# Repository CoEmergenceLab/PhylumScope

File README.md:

# Mechanical Design

# Electronics

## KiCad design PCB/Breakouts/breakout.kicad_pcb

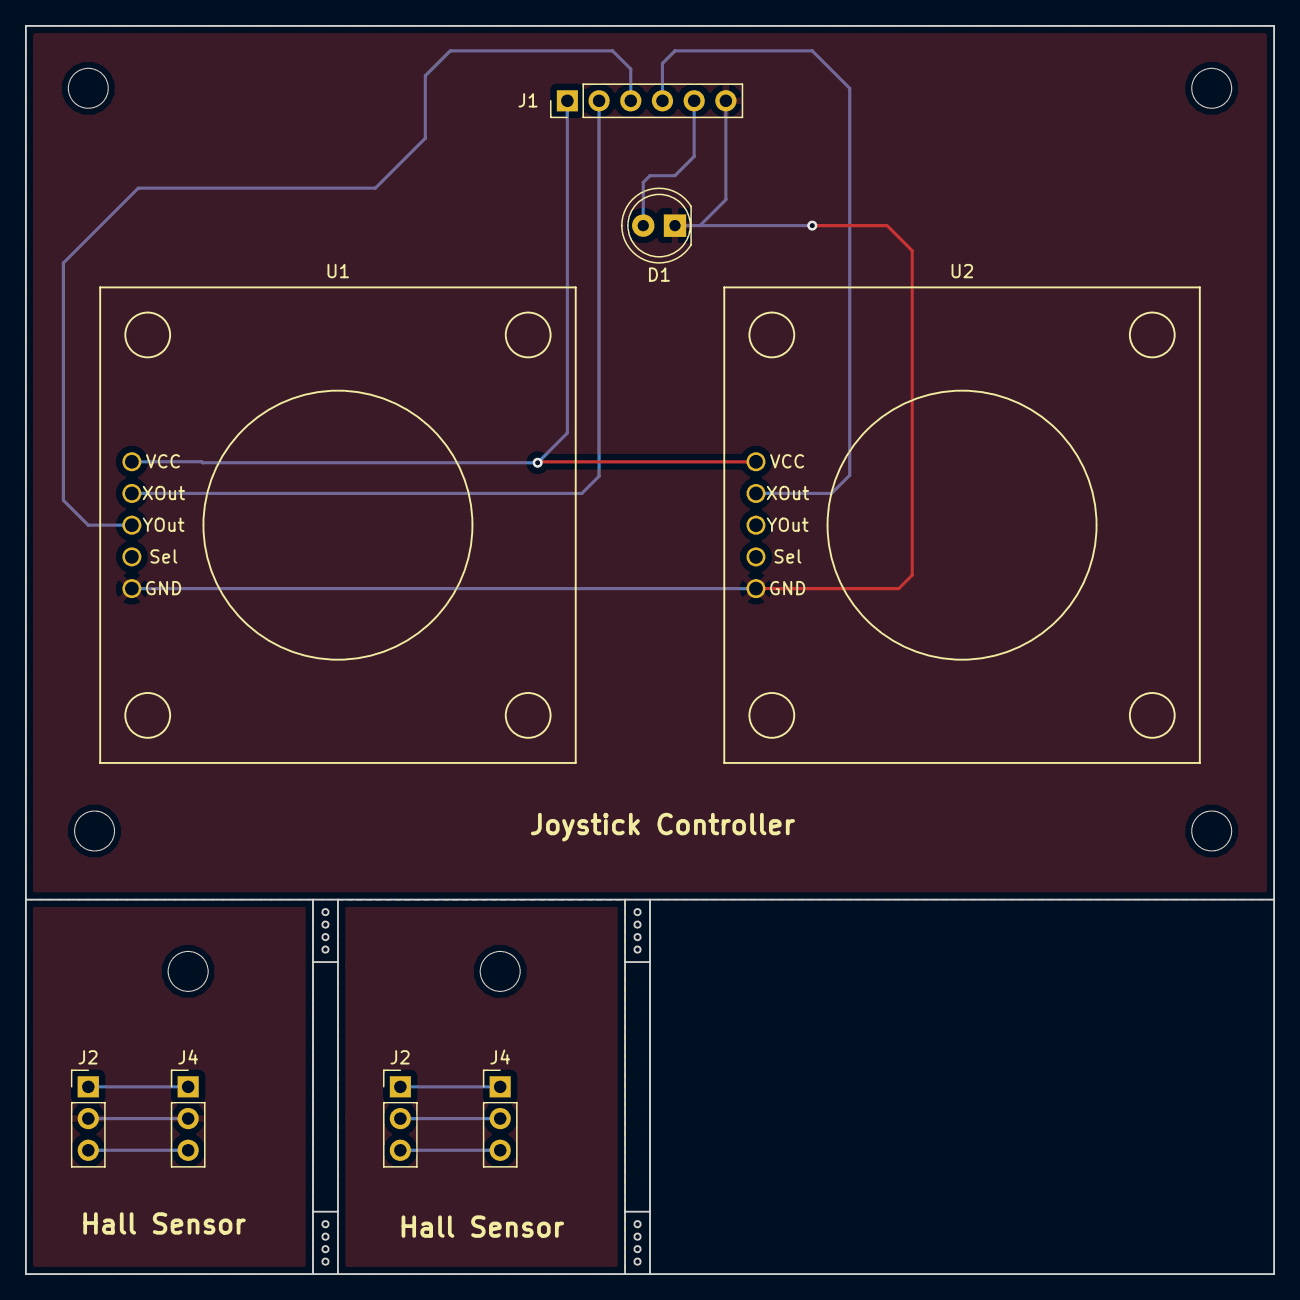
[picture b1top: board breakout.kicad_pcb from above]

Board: 2 copper layers, 100.0 x 100.0 mm, 8 parts (0 on the bottom side), 9 nets.

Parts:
D1: LED; LED_D5.0mm
J1: PinHeader_1x06_P2.54mm_Vertical
J2, J2#2: PinHeader_1x03_P2.54mm_Vertical
J4, J4#2: Hall; PinHeader_1x03_P2.54mm_Vertical
U1: Joystick_XY; ADA_joystick
U2: Joystick_Z; ADA_joystick

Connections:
unnamed: D1.1, J1.6, U1.5, U2.5
unnamed: D1.2, J1.5
unnamed: J1.1, U1.1, U2.1
unnamed: J1.2, U1.2
unnamed: J1.3, U1.3
unnamed: J1.4, U2.2
unnamed: J2#2.1, J4#2.1
unnamed: J2#2.2, J4#2.2
unnamed: J2#2.3, J4#2.3

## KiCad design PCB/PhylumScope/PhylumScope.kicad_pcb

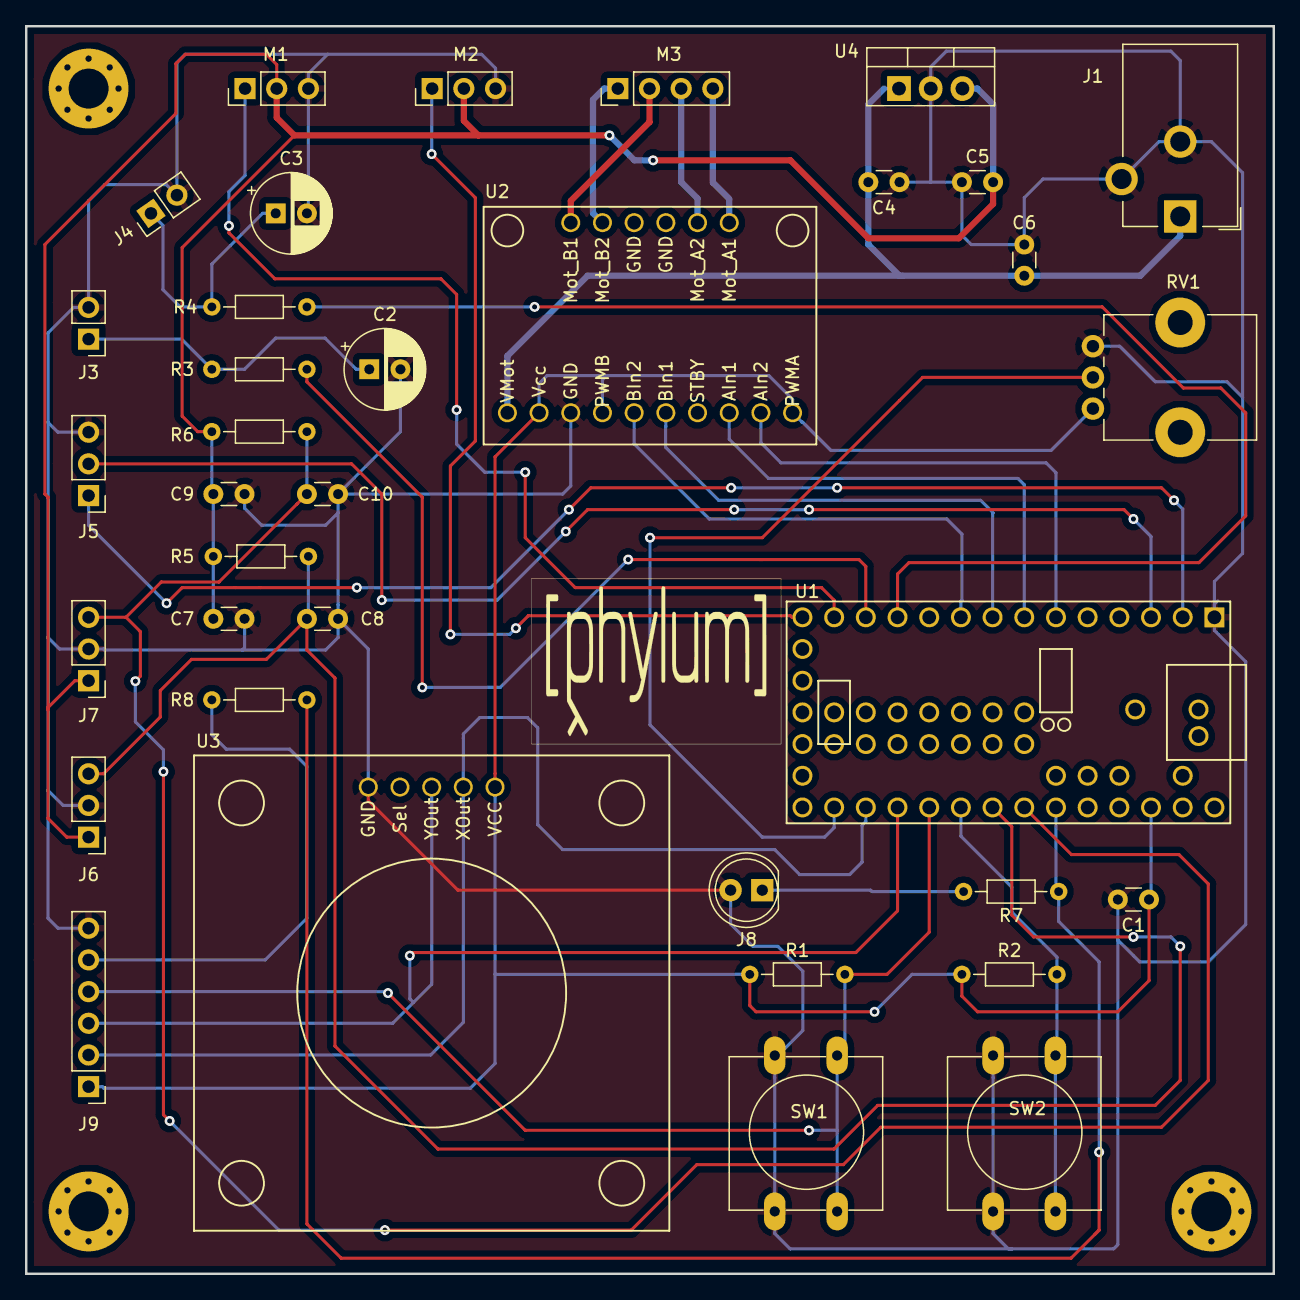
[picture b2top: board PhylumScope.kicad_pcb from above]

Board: 2 copper layers, 100.0 x 100.0 mm, 36 parts (0 on the bottom side), 30 nets.

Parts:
C1, C4, C5, C6: 0.1uF; C_Disc_D3.0mm_W1.6mm_P2.50mm
C2, C3: 47uF; CP_Radial_D6.3mm_P2.50mm
C7, C9: 100nF; C_Disc_D3.0mm_W1.6mm_P2.50mm
C8, C10: 4.7nF; C_Disc_D3.0mm_W1.6mm_P2.50mm
J1: +12V; BarrelJack_CUI_PJ-102AH_Horizontal
J3: LED2; PinHeader_1x02_P2.54mm_Vertical
J4: LED1; PinHeader_1x02_P2.54mm_Vertical
J5: RX/TX1; PinHeader_1x03_P2.54mm_Vertical
J6: Hall_L; PinHeader_1x03_P2.54mm_Vertical
J7: Hall_H; PinHeader_1x03_P2.54mm_Vertical
J8: LED3; LED_D5.0mm
J9: Controller; PinHeader_1x06_P2.54mm_Vertical
M1: Servo_X; PinHeader_1x03_P2.54mm_Vertical
M2: Servo_Y; PinHeader_1x03_P2.54mm_Vertical
M3: Stepper_Z; PinHeader_1x04_P2.54mm_Vertical
R1, R2, R5, R6: 10k; R_Axial_DIN0204_L3.6mm_D1.6mm_P7.62mm_Horizontal
R3, R4, R7, R8: 220Ω; R_Axial_DIN0204_L3.6mm_D1.6mm_P7.62mm_Horizontal
RV1: 10k; Potentiometer_Alps_RK09K_Single_Vertical
SW1: Z_UP; SW_PUSH-12mm
SW2: Z_DOWN; SW_PUSH-12mm
U1: Teensy3.2; Teensy30_31_32_All_Pins
U2: TB6612; ADA_TB6612
U3: Joystick; ADA_joystick
U4: LM7805; TO-220-3_Vertical

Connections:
+3.3V_bus: C1.1, J9.1, R1.1, R2.1, RV1.1, U1.31, U2.2, U2.4, U2.10, U3.1
+5V_bus: C5.2, C7.1, C9.1, J6.1, J7.1, M1.2, M2.2, R5.1, R6.1, U4.3
+12V_bus: C4.2, C6.2, J1.1, U2.1, U4.1
Btn_1: J9.4, R1.2, SW1.2, U1.24
Btn_2: R2.2, SW2.2, U1.25
GND: C1.2, C2.2, C3.2, C4.1, C5.1, C6.1, C7.2, C8.2, C9.2, C10.2, J1.2, J1.3, J3.2, J4.2, J5.3, J6.2, J7.2, J8.2, J9.6, M1.3, M2.3, RV1.3, SW1.1, SW2.1, U1.1, U2.3, U3.5, U4.2
Hall_H: C10.1, J7.3, R6.2, U1.27
Hall_L: C8.1, J6.3, R5.2, U1.26
Joy_X: J9.2, U1.22, U3.2
Joy_Y: J9.3, U1.23, U3.3
LED_1: R4.1, U1.11
LED_2: R3.1, U1.12
LED_3: R7.1, R8.1, U1.28
unnamed: C2.1, J3.1, R3.2
unnamed: C3.1, J4.1, R4.2
unnamed: J8.1, R7.2
unnamed: J9.5, R8.2
unnamed: M3.1, U2.15
unnamed: M3.2, U2.16
unnamed: M3.3, U2.12
unnamed: M3.4, U2.11
unnamed: RV1.2, U1.21
RX_1: J5.1, U1.2
Servo_X: M1.1, U1.13
Servo_Y: M2.1, U1.14
Stepper_Z_AIn1: U1.7, U2.8
Stepper_Z_AIn2: U1.6, U2.9
Stepper_Z_BIn1: U1.8, U2.6
Stepper_Z_BIn2: U1.9, U2.5
TX_1: J5.2, U1.3

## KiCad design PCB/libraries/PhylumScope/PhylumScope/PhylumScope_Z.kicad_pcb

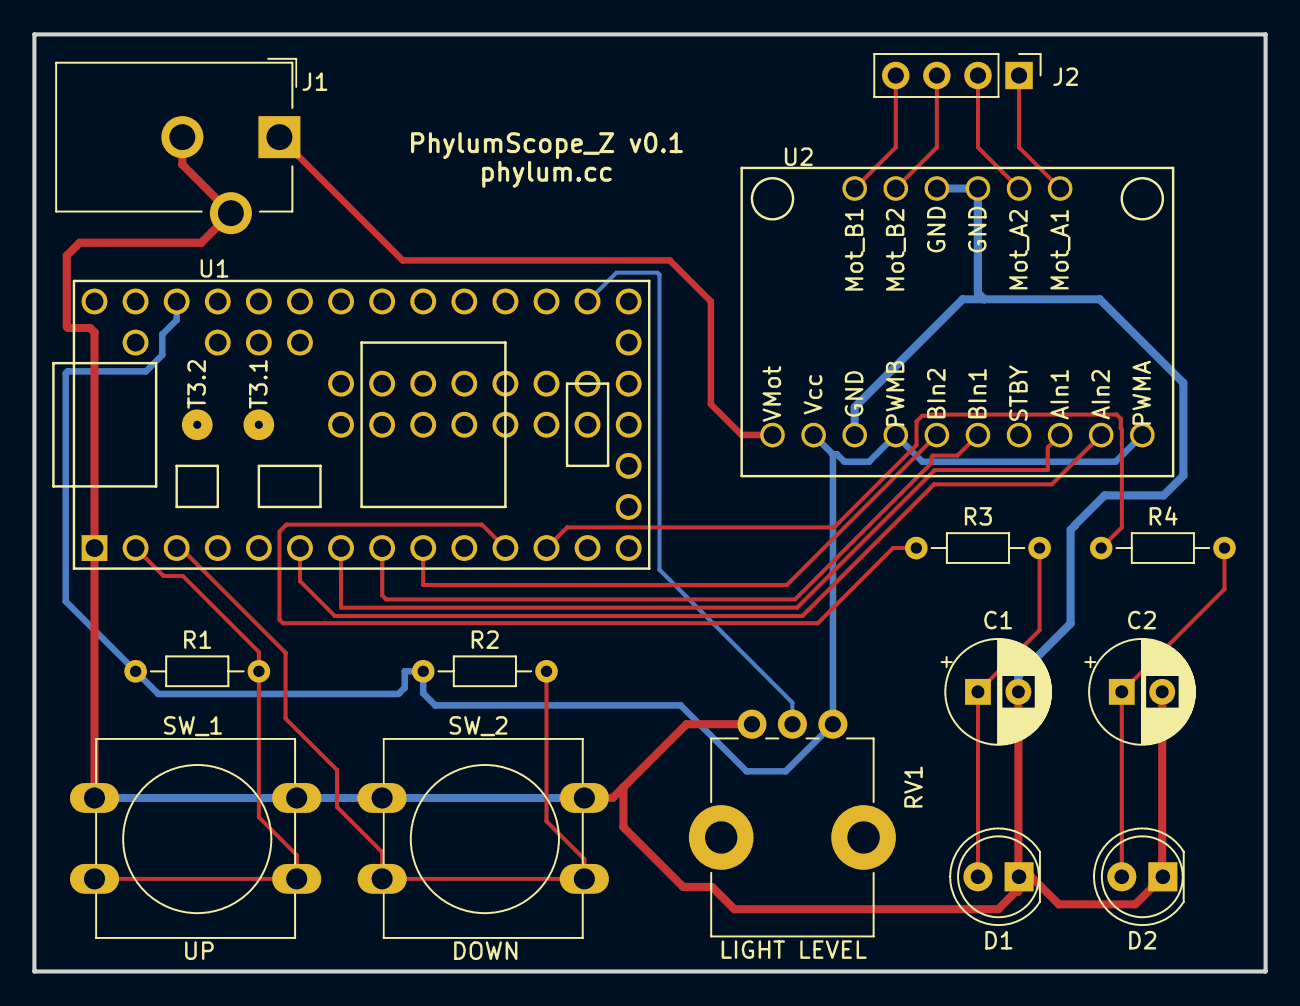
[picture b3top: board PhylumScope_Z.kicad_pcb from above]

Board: 2 copper layers, 76.1 x 57.9 mm, 15 parts (0 on the bottom side), 18 nets.

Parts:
C1, C2: 100uF; CP_Radial_D6.3mm_P2.50mm
D1, D2: LED; LED_D5.0mm
J1: +12V (Stepper_Z); BarrelJack_CUI_PJ-102AH_Horizontal
J2: Stepper_Z; PinHeader_1x04_P2.54mm_Vertical
R1, R2: 10k; R_Axial_DIN0204_L3.6mm_D1.6mm_P7.62mm_Horizontal
R3, R4: 220Ω (1% tol); R_Axial_DIN0204_L3.6mm_D1.6mm_P7.62mm_Horizontal
RV1: 10k; Potentiometer_Alps_RK09K_Single_Vertical
SW_1, SW_2: SW_PUSH; SW_PUSH-12mm
U1: Teensy3.2; Teensy30_31_32_LC_Interspecifics
U2: TB6612; ADA_TB6612

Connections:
+12V: J1.1, U2.1
/+3.3V: R1.1, R2.1, RV1.3, U1.31, U2.2, U2.4, U2.10
GND: C1.2, C2.2, D1.1, D2.1, J1.2, J1.3, RV1.1, SW_1.1, SW_2.1, U1.1, U2.3, U2.13, U2.14
unnamed: C1.1, D1.2, R3.2
unnamed: C2.1, D2.2, R4.2
unnamed: J2.1, U2.11
unnamed: J2.2, U2.12
unnamed: J2.3, U2.15
unnamed: J2.4, U2.16
unnamed: R1.2, SW_1.2, U1.2
unnamed: R2.2, SW_2.2, U1.3
unnamed: R3.1, U1.11
unnamed: R4.1, U1.12
unnamed: RV1.2, U1.21
unnamed: U1.6, U2.9
unnamed: U1.7, U2.8
unnamed: U1.8, U2.6
unnamed: U1.9, U2.5

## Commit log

2021-06-29 CAD design, STL files
    - AutoCAD design.
    - STL files for 3D printed adapter and stabilizer parts.
    - Design does not include Microscope attachment.
2021-06-30 PCB Libraries
2021-06-30 KiCAD - Schematic, Layout
2021-07-08 XY axis
    Under Construction: Yrack, Yrack base, Yrack top.
    Completed: Xgear, Xrack, Ygear, servo arm.
2021-07-09 Completed XY axis
2021-07-10 Breakout Boards - KiCad
    - Schematic, Layout and 3D file for external controller and hall effect sensors
2021-07-10 PCB gerber files
    - Main board
    - Breakout boards
2021-07-17 Z-axis improved tolerances
2021-07-17 XY axis
2021-07-23 Breakouts V-Cut update, Zipped Gerbers
2021-08-20 Optical Flow
2021-08-20 Test programs for XY and Z axis
2021-08-20 Serial tests
